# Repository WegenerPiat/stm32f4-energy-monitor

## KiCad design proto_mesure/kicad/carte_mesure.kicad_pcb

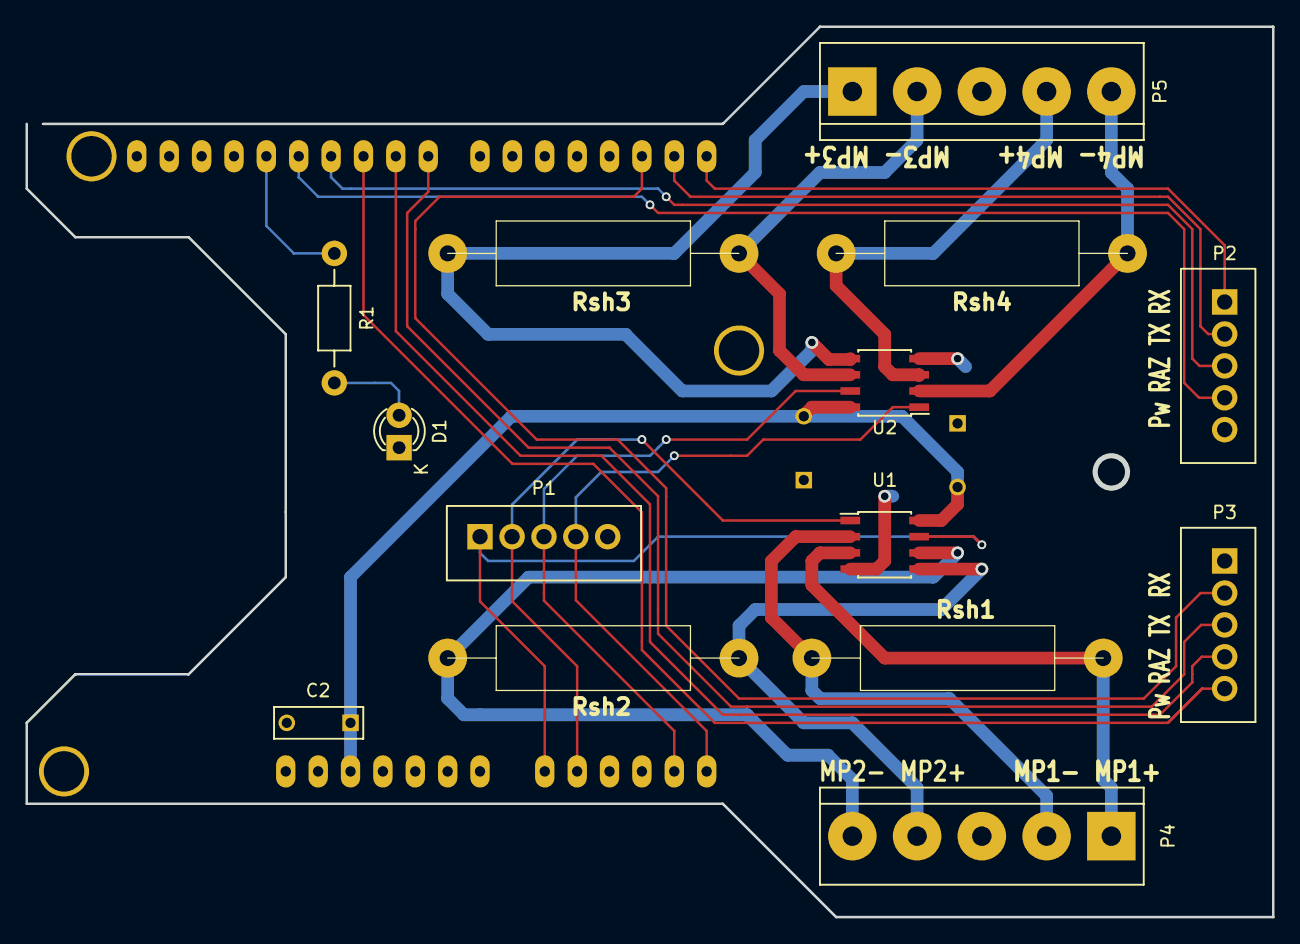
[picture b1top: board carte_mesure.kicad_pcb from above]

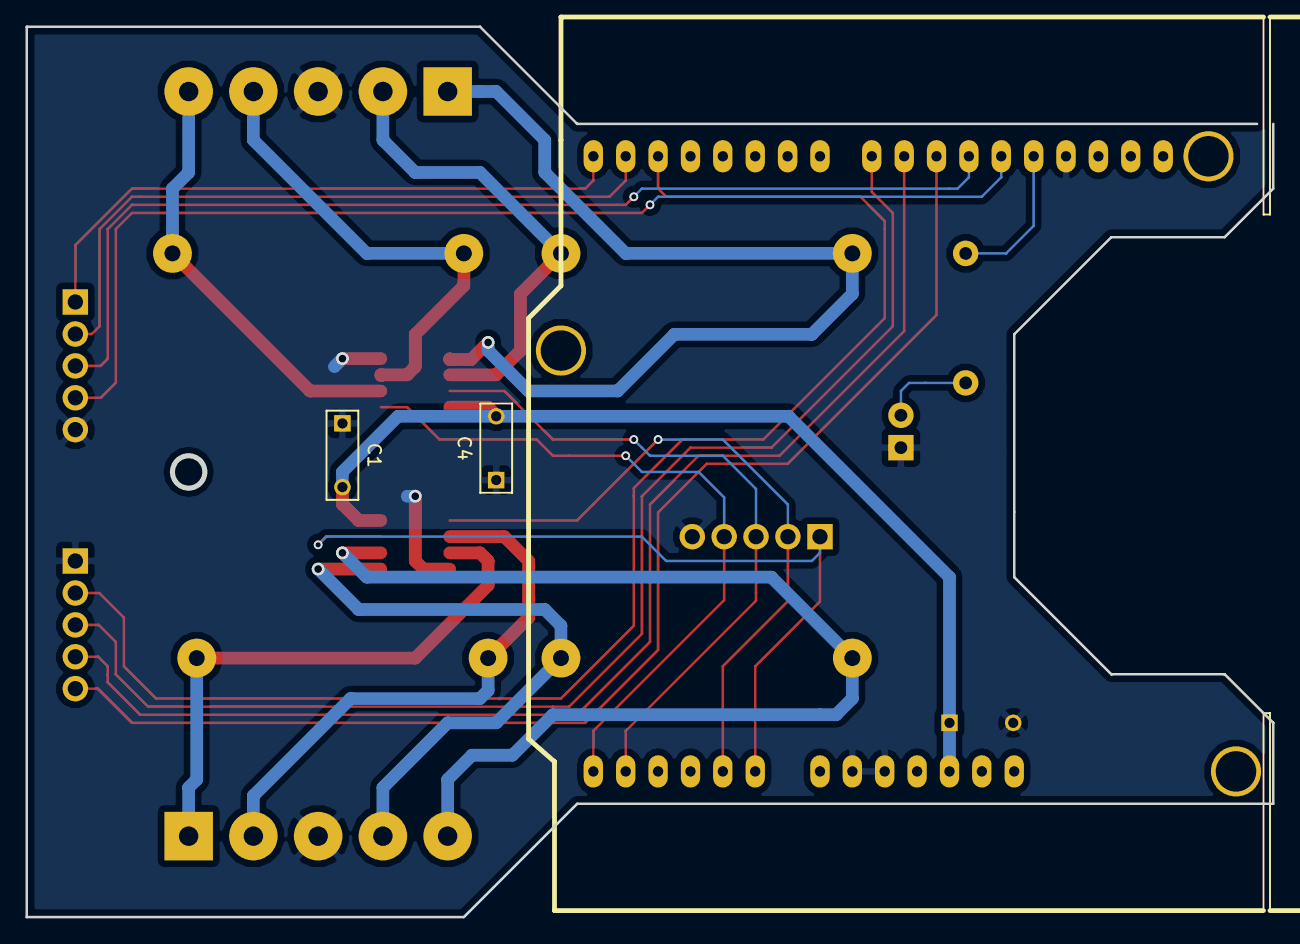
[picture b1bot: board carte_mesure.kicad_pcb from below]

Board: 2 copper layers, 97.8 x 69.8 mm, 17 parts (2 on the bottom side), 24 nets.

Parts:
C1, C2, C4: 100nF; C_Rect_L7_W2.5_P5
D1: LED; LED-3MM
P1, P2, P3: CONN_01X05; Wafer_Vertical15x5.8x7RM2.5-5
P4, P5: CONN_01X05; bornier5
R1: 680R; Resistor_Horizontal_RM10mm
Rsh1, Rsh2, Rsh3, Rsh4: Shunt; shunt
SHIELD1: ARDUINO_SHIELD_NUCLEO
U1, U2: MAX4377; SOIC-8_3.9x4.9mm_Pitch1.27mm

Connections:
+3V3: C1.2, C2.1, C4.2, SHIELD1.3V3, U1.8, U2.8
/carte_nucleo/MP_A1: P1.1, SHIELD1.AD0, U1.7
/carte_nucleo/MP_A2: P1.2, SHIELD1.AD1, U1.1
/carte_nucleo/MP_B1: P1.3, SHIELD1.AD4, U2.7
/carte_nucleo/MP_B2: P1.4, SHIELD1.AD5, U2.1
/carte_nucleo/PWD1: P2.4, SHIELD1.D12
/carte_nucleo/PWD2: P3.5, SHIELD1.D10
/carte_nucleo/RX1: P2.1, SHIELD1.D0
/carte_nucleo/RX2: P3.2, SHIELD1.D2
/carte_nucleo/Reset1: P2.3, SHIELD1.D11
/carte_nucleo/Reset2: P3.4, SHIELD1.D9
/carte_nucleo/TX1: P2.2, SHIELD1.D1
/carte_nucleo/TX2: P3.3, SHIELD1.D8
/conn_shunt1/MP1+: P4.1, Rsh1.+, U1.3
/conn_shunt1/MP1-: P4.2, Rsh1.-, U1.2
/conn_shunt1/MP2+: P4.4, Rsh2.+, U1.5
/conn_shunt1/MP2-: P4.5, Rsh2.-, U1.6
/conn_shunt_MES2/MP3+: P5.1, Rsh3.+, U2.5
/conn_shunt_MES2/MP3-: P5.2, Rsh3.-, U2.6
/conn_shunt_MES2/MP4+: P5.4, Rsh4.+, U2.3
/conn_shunt_MES2/MP4-: P5.5, Rsh4.-, U2.2
GND: C1.1, C2.2, C4.1, D1.1, P1.5, P2.5, P3.1, P4.3, P5.3, SHIELD1.GND1, SHIELD1.GND2, SHIELD1.GND3, U1.4, U2.4
unnamed: D1.2, R1.2
unnamed: R1.1, SHIELD1.D13

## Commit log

2016-08-31 ancienne version (version d'origine)
2016-08-31 fonctionnement pour la carte stm32_F4 Discovery avec le premier shield
2016-08-31 intégration du buffer, écriture des données dans un fichier texte
2016-08-31 intégration d'un tableau de données à transmettre et afficher. (ne fonctionne pas encore)
2016-08-31 dernier code fonctionnant (energy_monitor_buff)
2016-08-31 ajout du dossier Kicad
